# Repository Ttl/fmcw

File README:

Frequency modulated radar hardware, firmware and processing files.

For more information see:

http://hforsten.com/6-ghz-frequency-modulated-radar.html

and

http://hforsten.com/homemade-synthetic-aperture-radar.html

List of contents:

hardware: Contains KiCad schematic and board files. Made using KiCad version 2014-10-17 and might not open with a too old version.

firmware: Firmware for the Freescale Kinetis KL26Z microcontroller. Should be opened using Kinetis Design Studio (http://www.freescale.com/webapp/sps/site/prod_summary.jsp?code=KDS_IDE).

Firmware depends on mcuoneclipse components available at here: http://sourceforge.net/projects/mcuoneclipse/files/PEx%20Components/

processing: PC code for using the radar and processing the resulting data.
"fmcw.py" uses the radar and logs the data.
"fmcw_process.py" process the recorded data and plots time-range plot of them.
"list_plot.py" plots individual sweep captures from the recorded data for debugging purposes.

simulations: CST Microwave studio files.

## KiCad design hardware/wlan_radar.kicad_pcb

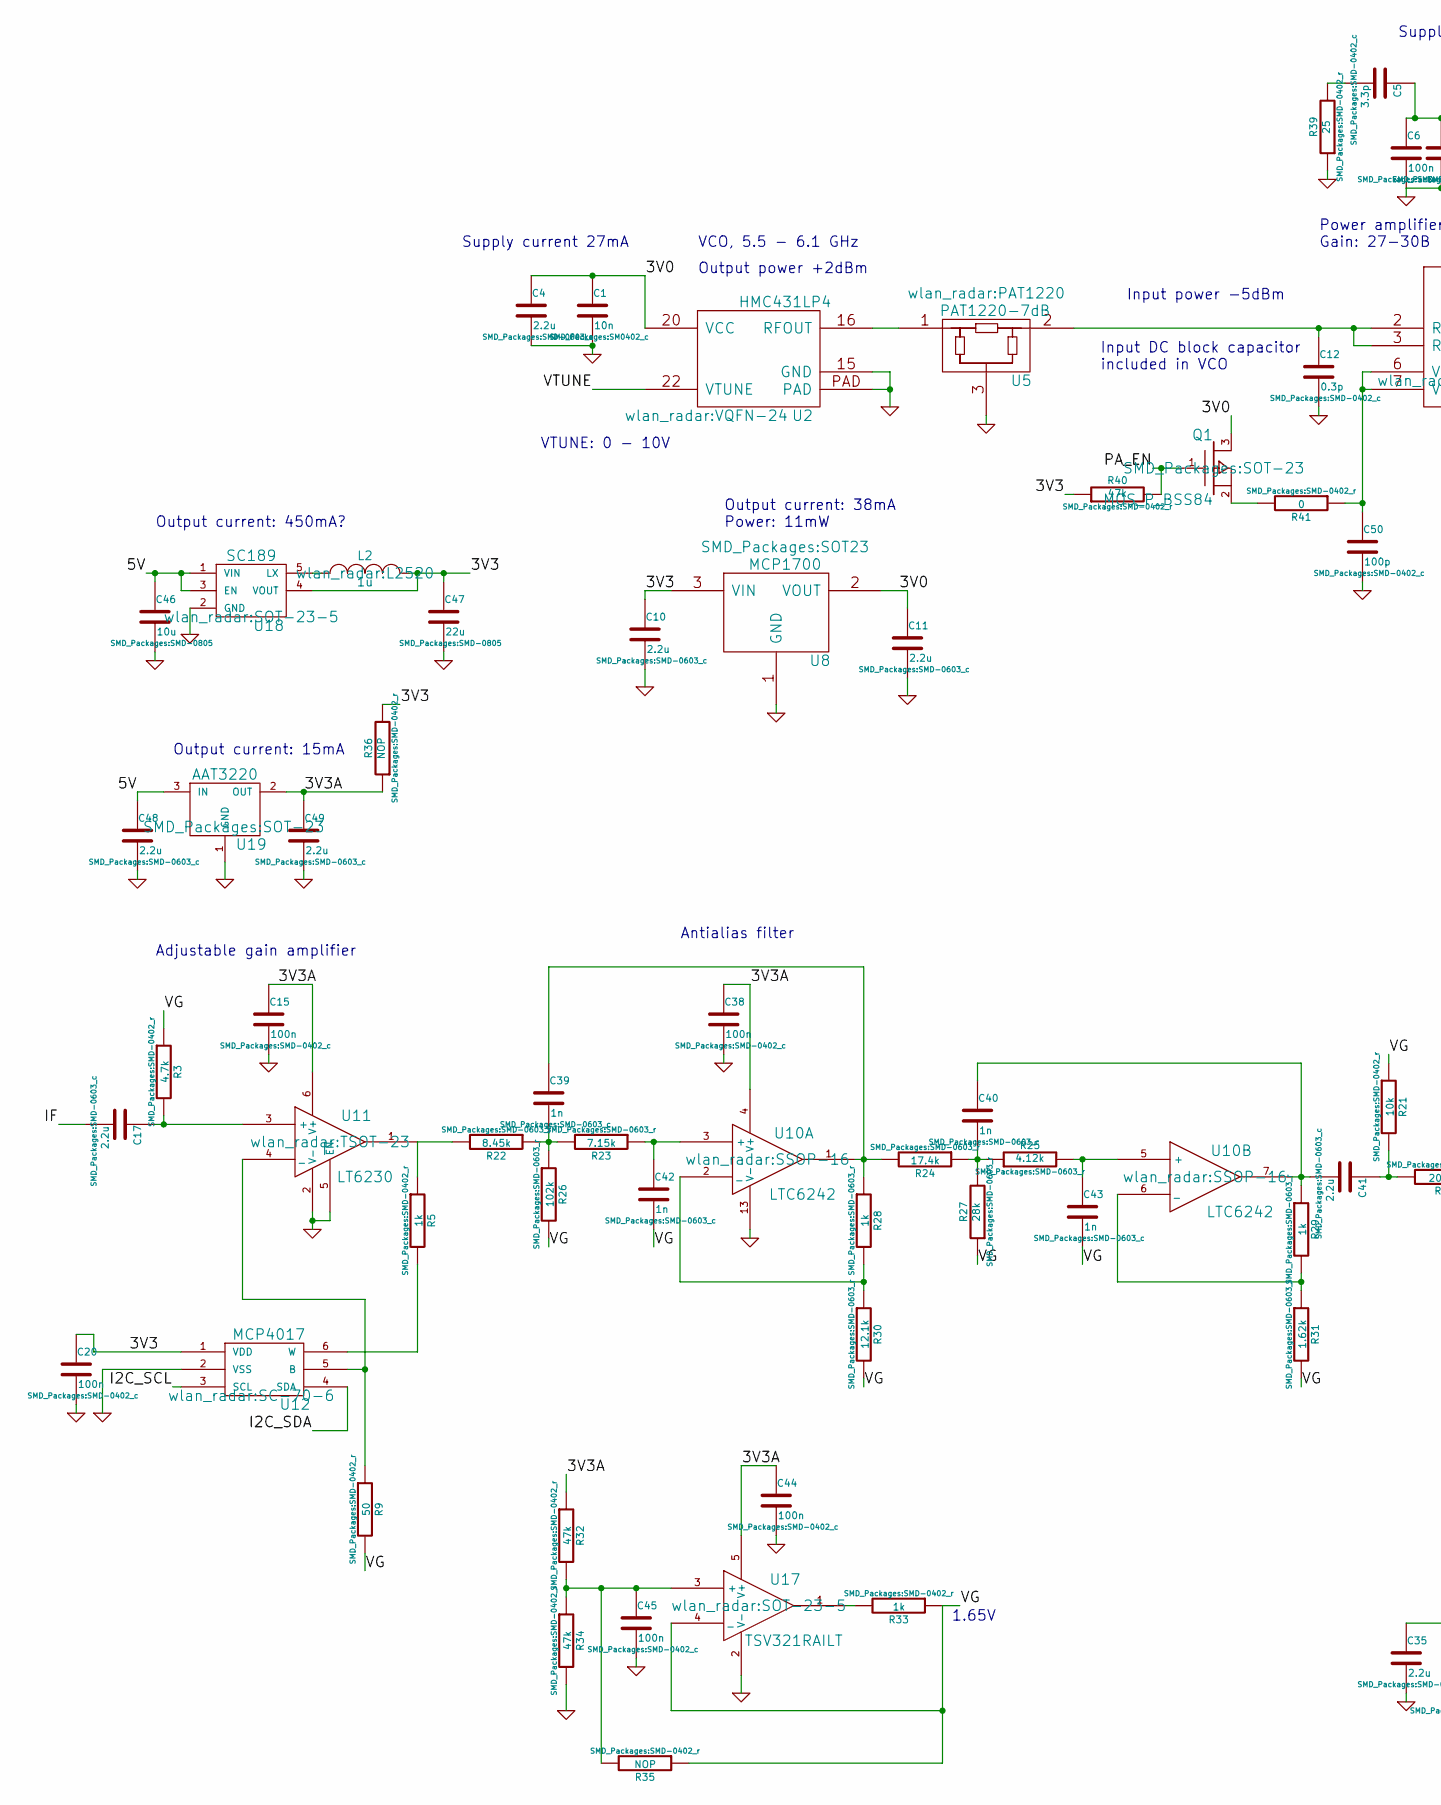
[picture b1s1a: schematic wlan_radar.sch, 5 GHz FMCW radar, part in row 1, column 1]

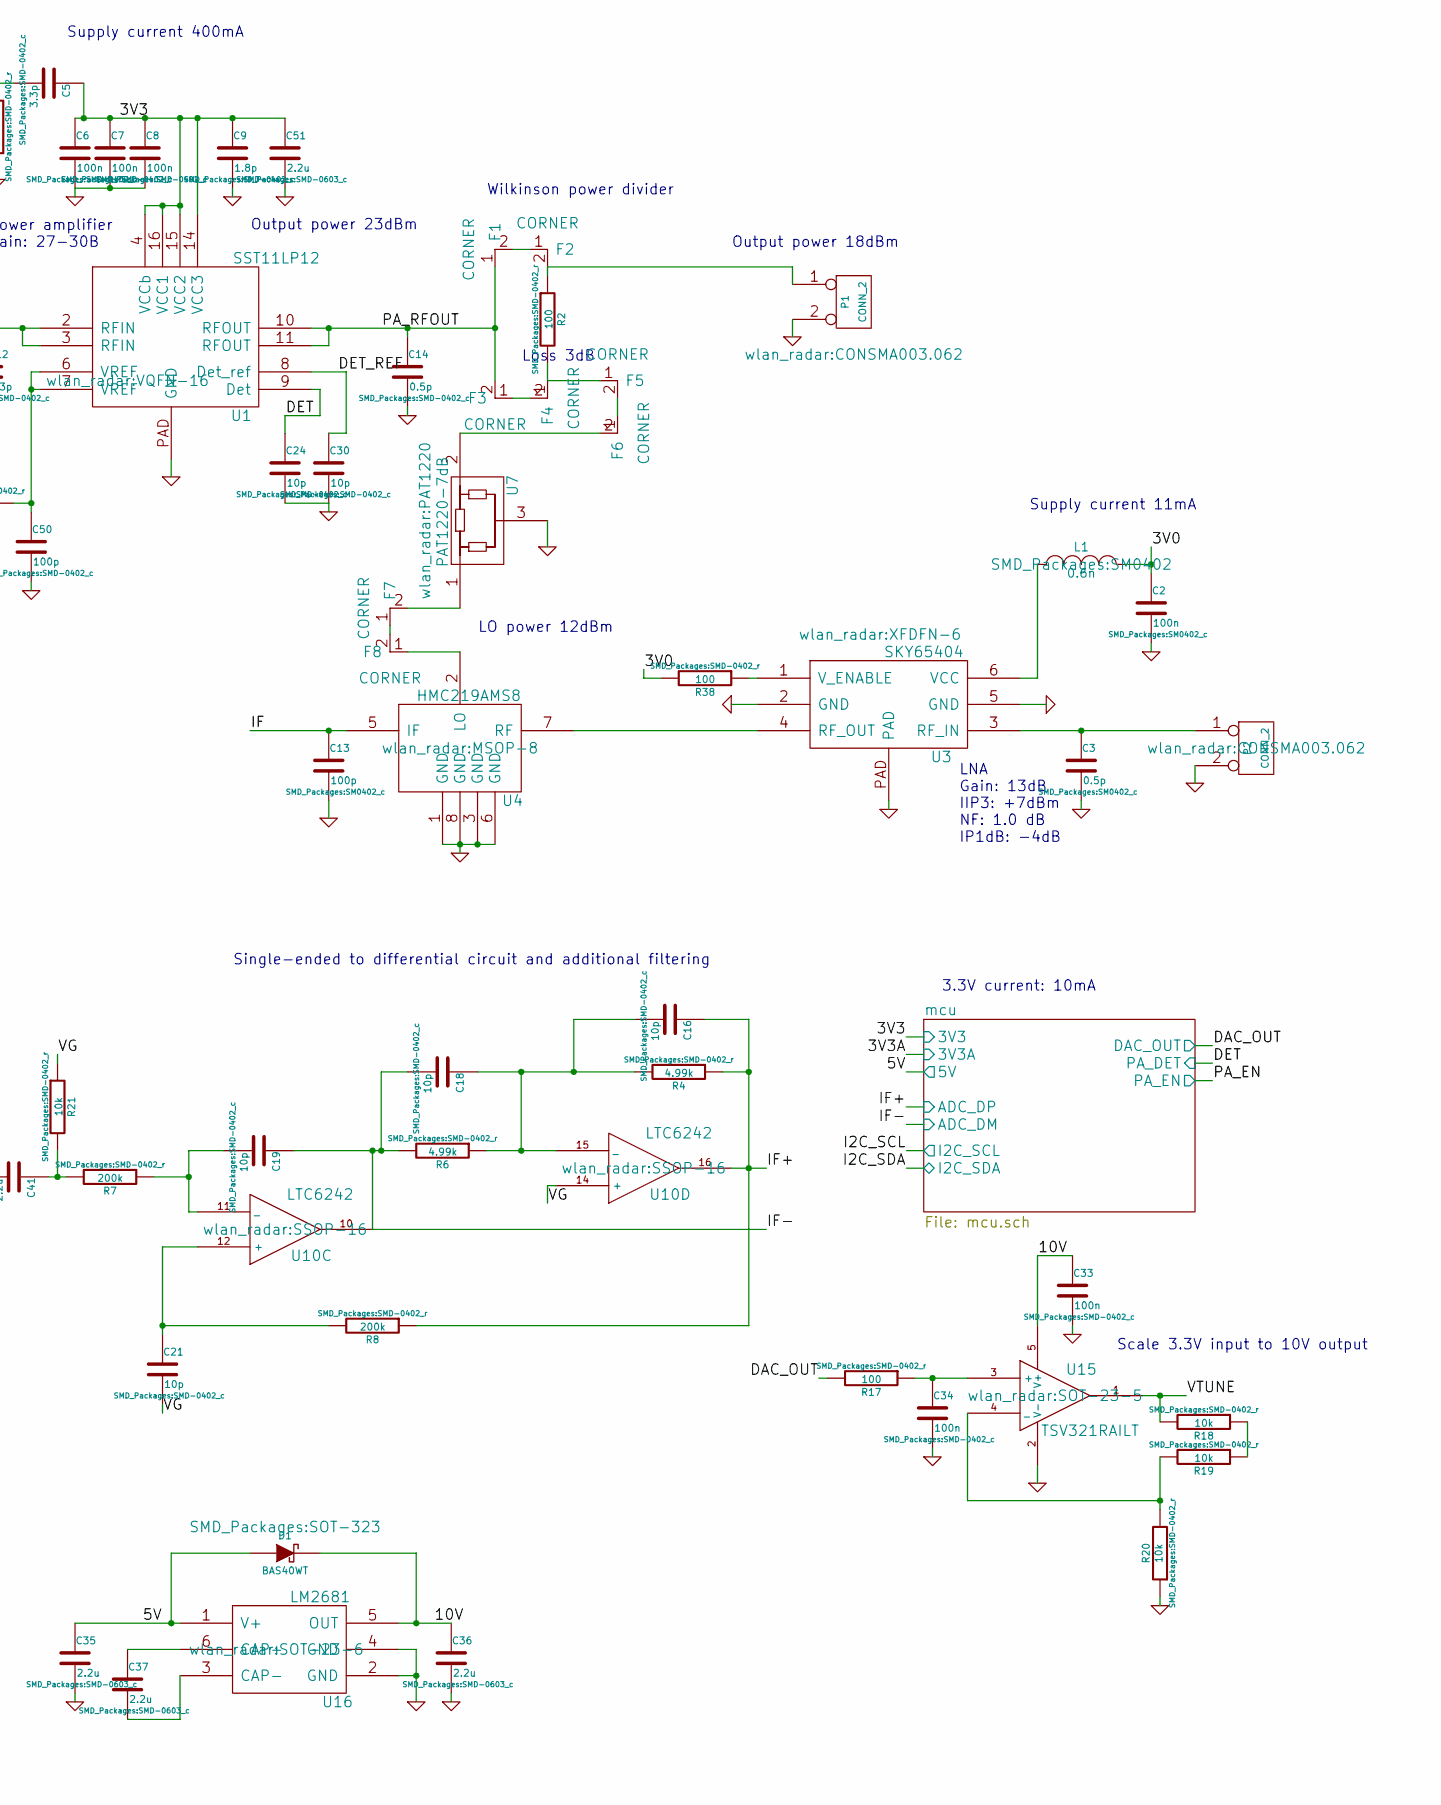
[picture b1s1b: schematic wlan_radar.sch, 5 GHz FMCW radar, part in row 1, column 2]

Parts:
C1: 10n; SM0402_c
C2: 100n; SM0402_c
C3: 0.5p; SM0402_c
C4, C10, C11, C17, C35, C36, C37, C41, C48, C49, C51: 2.2u; SMD-0603_c
C5: 3.3p; SMD-0402_c
C6, C7, C8, C15, C20, C33, C34, C38, C44, C45: 100n; SMD-0402_c
C9: 1.8p; SMD-0402_c
C12: 0.3p; SMD-0402_c
C13: 100p; SM0402_c
C14: 0.5p; SMD-0402_c
C16, C18, C19, C21, C24, C30: 10p; SMD-0402_c
C39, C40, C42, C43: 1n; SMD-0603_c
C46: 10u; SMD-0805
C47: 22u; SMD-0805
C50: 100p; SMD-0402_c
D1: BAS40WT; SOT-323
F1, F2, F3, F4: CORNER; miter_0.179_90deg
F5, F6, F7, F8: CORNER; MITER_0.350mm_90deg
L1: 0.6n; SM0402
L2: 1u; L2520
P1, P2: CONN_2; CONSMA003.062
Q1: MOS_P_BSS84; SOT-23
R2, R17, R38: 100; SMD-0402_r
R3: 4.7k; SMD-0402_r
R4, R6: 4.99k; SMD-0402_r
R5, R33: 1k; SMD-0402_r
R7, R8: 200k; SMD-0402_r
R9: 50; SMD-0402_r
R18, R19, R20, R21: 10k; SMD-0402_r
R22: 8.45k; SMD-0603_r
R23: 7.15k; SMD-0603_r
R24: 17.4k; SMD-0603_r
R25: 4.12k; SMD-0603_r
R26: 102k; SMD-0603_r
R27: 28k; SMD-0603_r
R28, R29: 1k; SMD-0603_r
R30: 12.1k; SMD-0603_r
R31: 1.62k; SMD-0603_r
R32, R34, R40: 47k; SMD-0402_r
R35, R36: NOP; SMD-0402_r
R39: 25; SMD-0402_r
R41: 0; SMD-0402_r
U1: SST11LP12; VQFN-16
U2: HMC431LP4; VQFN-24
U3: SKY65404; XFDFN-6
U4: HMC219AMS8; MSOP-8
U5, U7: PAT1220-7dB; PAT1220
U8: MCP1700; SOT23
U10: LTC6242; SSOP-16
U11: LT6230; TSOT-23
U12: MCP4017; SC-70-6
U15, U17: TSV321RAILT; SOT-23-5
U16: LM2681; SOT-23-6
U18: SC189; SOT-23-5
U19: AAT3220; SOT-23

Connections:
/3V0: C1.1, C2.1, C4.1, C11.1, L1.2, Q1.3 (D), R38.2, U2.20 (VCC), U8.2 (VOUT)
/10V: C33.1, C36.1, D1.3 (K), U15.5 (V+), U16.5 (OUT)
/DET_REF: C30.1, U1.8 (Det_ref)
/IF: C13.1, C17.2, U4.5 (IF)
/PA_RFOUT: C14.1, F1.1, F3.2, U1.10 (RFOUT), U1.11 (RFOUT)
/VG: C21.2, C42.2, C43.2, R3.1, R9.2, R21.1, R26.2, R27.1, R30.2, R31.2, R33.1, R35.1, U10.14 (+), U17.4 (_)
/VTUNE: R18.2, U2.22 (VTUNE), U15.1
/mcu/3V3: C5.1, C6.1, C7.1, C8.1, C9.1, C10.1, C20.1, C47.1, C51.1, L2.2, R36.2, R40.1, U1.4 (VCCb), U1.14 (VCC3), U1.15 (VCC2), U1.16 (VCC1), U8.3 (VIN), U12.1 (VDD), U18.4 (VOUT); also elsewhere on the board
/mcu/3V3A: C15.1, C38.1, C44.1, C49.1, R32.1, R36.1, U10.4 (V+), U11.6 (V+), U17.5 (V+), U19.2 (OUT); also elsewhere on the board
/mcu/5V: C35.1, C46.1, C48.1, D1.1 (A), U16.1 (V+), U18.1 (VIN), U18.3 (EN), U19.3 (IN); also elsewhere on the board
/mcu/ADC_DM: C18.2, C19.1, R6.2, U10.10; also elsewhere on the board
/mcu/ADC_DP: C16.1, R4.1, R8.1, U10.16; also elsewhere on the board
/mcu/DAC_OUT: R17.2; also elsewhere on the board
/mcu/I2C_SCL: U12.3 (SCL); also elsewhere on the board
/mcu/I2C_SDA: U12.4 (SDA); also elsewhere on the board
/mcu/PA_DET: C24.1, U1.9 (Det); also elsewhere on the board
/mcu/PA_EN: Q1.1 (G), R40.2; also elsewhere on the board
GND: C1.2, C2.2, C3.2, C4.2, C6.2, C7.2, C8.2, C9.2, C10.2, C11.2, C12.2, C13.2, C14.2, C15.2, C20.2, C24.2, C30.2, C33.2, C34.2, C35.2, C36.2, C38.2, C44.2, C45.2, C46.2, C47.2, C48.2, C49.2, C50.2, C51.2, P1.2 (PM), P2.2 (PM), R20.1, R34.2, R39.1, U1.PAD (GND), U2.15 (GND), U2.PAD, U3.2 (GND), U3.5 (GND), U3.PAD, U4.1 (GND), U4.3 (GND), U4.6 (GND), U4.8 (GND), U5.3, U7.3, U8.1 (GND), U10.13 (V-), U11.2 (V-), U11.5 (~EN), U12.2 (VSS), U15.2 (V-), U16.2 (GND), U16.4 (GND), U17.2 (V-), U18.2 (GND), U19.1 (GND); also elsewhere on the board
unnamed: C3.1, P2.1, U3.3 (RF_IN)
unnamed: C5.2, R39.2
unnamed: C12.1, U1.2 (RFIN), U1.3 (RFIN), U5.2
unnamed: C16.2, C18.1, R4.2, R6.1, U10.15 (_)
unnamed: C17.1, R3.2, U11.3 (+)
unnamed: C19.2, R7.1, U10.11 (_)
unnamed: C21.1, R8.2, U10.12 (+)
unnamed: C34.1, R17.1, U15.3 (+)
unnamed: C37.1, U16.6 (CAP+)
unnamed: C37.2, U16.3 (CAP-)
unnamed: C39.1, R24.2, R28.1, U10.1
unnamed: C39.2, R22.1, R23.2, R26.1
unnamed: C40.1, C41.2, R29.1, U10.7
unnamed: C40.2, R24.1, R25.1, R27.2
unnamed: C41.1, R7.2, R21.2
unnamed: C42.1, R23.1, U10.3 (+)
unnamed: C43.1, R25.2, U10.5 (+)
unnamed: C45.1, R32.2, R34.1, R35.2, U17.3 (+)
unnamed: C50.1, R41.1, U1.6 (VREF), U1.7 (VREF)
unnamed: F1.2, F2.1
unnamed: F2.2, P1.1, R2.1
unnamed: F3.1, F4.2
unnamed: F4.1, F5.1, R2.2
unnamed: F5.2, F6.1
unnamed: F6.2, U7.2
unnamed: F7.1, F8.2
unnamed: F7.2, U7.1
unnamed: F8.1, U4.2 (LO)
unnamed: L1.1, U3.6 (VCC)
unnamed: L2.1, U18.5 (LX)
unnamed: Q1.2 (S), R41.2
unnamed: R5.2, U12.6 (W)
unnamed: R9.1, U11.4 (_), U12.5 (B)
unnamed: R18.1, R19.1
unnamed: R19.2, R20.2, U15.4 (_)
unnamed: R5.1, R22.2, U11.1
unnamed: R28.2, R30.1, U10.2 (_)
unnamed: R29.2, R31.1, U10.6 (_)
unnamed: R33.2, U17.1
unnamed: R38.1, U3.1 (V_ENABLE)
unnamed: U2.16 (RFOUT), U5.1
unnamed: U3.4 (RF_OUT), U4.7 (RF)

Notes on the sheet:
VCO, 5.5 - 6.1 GHz
Output power +2dBm
Wilkinson power divider
Power amplifier Gain: 27-30B
Input power -5dBm
Output power 23dBm
Loss 3dB
Output power 18dBm
LO power 12dBm
LNA Gain: 13dB IIP3: +7dBm NF: 1.0 dB IP1dB: -4dB
Supply current 400mA
Supply current 27mA
VTUNE: 0 - 10V
Supply current 11mA
Output current: 38mA Power: 11mW
Scale 3.3V input to 10V output
1.65V
Adjustable gain amplifier
Antialias filter
Single-ended to differential circuit and additional filtering
Output current: 15mA
Output current: 450mA?
Input DC block capacitor included in VCO
3.3V current: 10mA

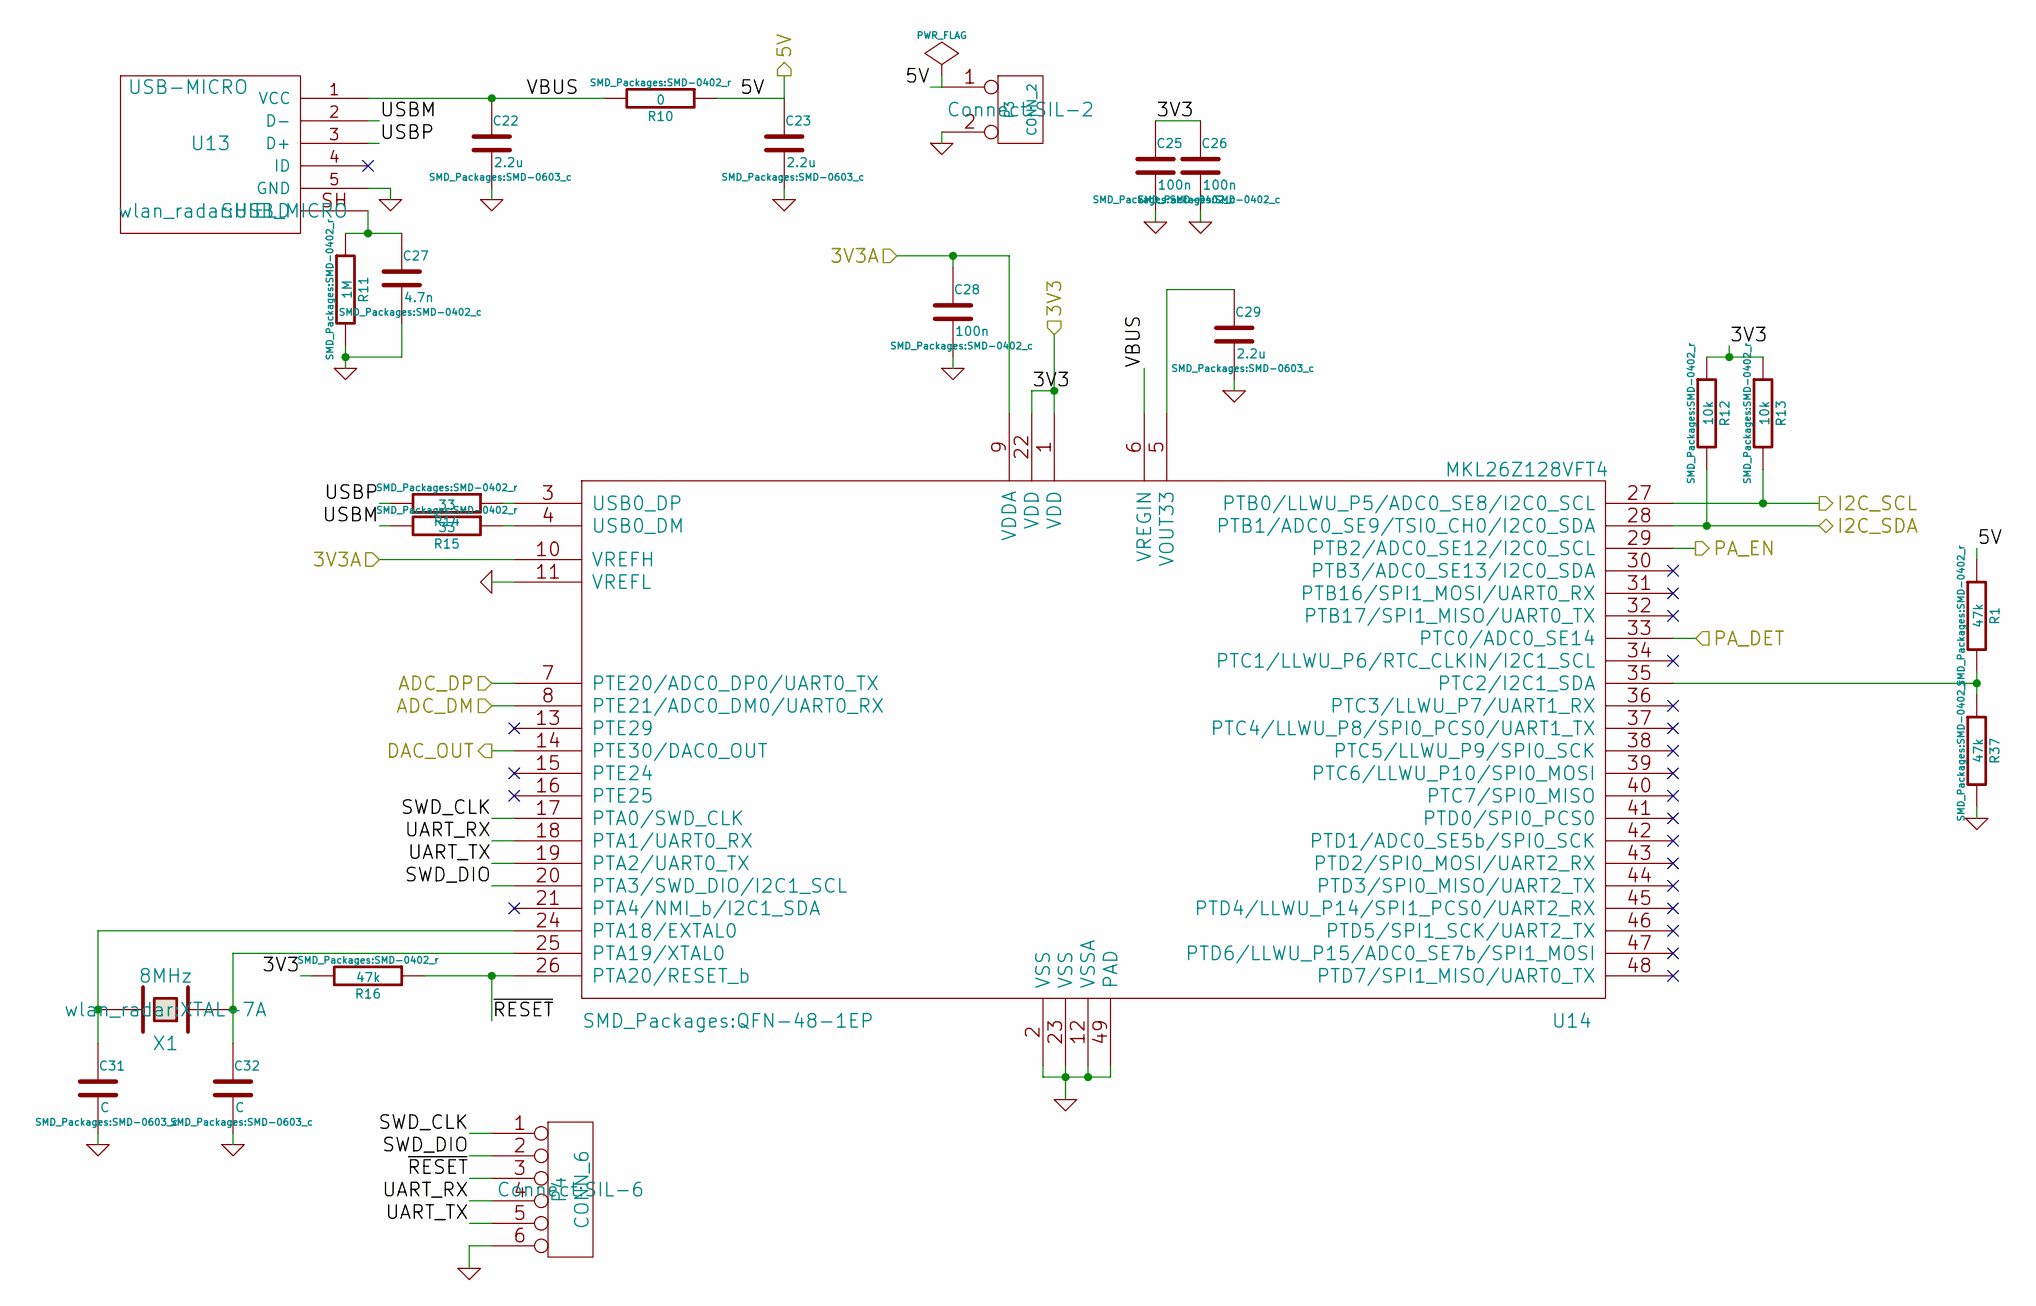
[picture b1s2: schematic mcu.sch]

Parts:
C22, C23, C29: 2.2u; SMD-0603_c
C25, C26, C28: 100n; SMD-0402_c
C27: 4.7n; SMD-0402_c
C31, C32: C; SMD-0603_c
P3: CONN_2; SIL-2
P4: CONN_6; SIL-6
R1, R16, R37: 47k; SMD-0402_r
R10: 0; SMD-0402_r
R11: 1M; SMD-0402_r
R12, R13: 10k; SMD-0402_r
R14, R15: 33; SMD-0402_r
U13: USB-MICRO; USB_MICRO
U14: MKL26Z128VFT4; QFN-48-1EP
X1: 8MHz; XTAL-7A

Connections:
/mcu/3V3: C25.1, C26.1, R12.1, R13.1, R16.2, U14.1 (VDD), U14.22 (VDD); also elsewhere on the board
/mcu/3V3A: C28.1, U14.9 (VDDA), U14.10 (VREFH); also elsewhere on the board
/mcu/5V: C23.1, P3.1, R1.1, R10.1; also elsewhere on the board
/mcu/ADC_DM: U14.8 (PTE21/ADC0_DM0/UART0_RX); also elsewhere on the board
/mcu/ADC_DP: U14.7 (PTE20/ADC0_DP0/UART0_TX); also elsewhere on the board
/mcu/DAC_OUT: U14.14 (PTE30/DAC0_OUT); also elsewhere on the board
/mcu/I2C_SCL: R13.2, U14.27 (PTB0/LLWU_P5/ADC0_SE8/I2C0_SCL); also elsewhere on the board
/mcu/I2C_SDA: R12.2, U14.28 (PTB1/ADC0_SE9/TSI0_CH0/I2C0_SDA); also elsewhere on the board
/mcu/PA_DET: U14.33 (PTC0/ADC0_SE14); also elsewhere on the board
/mcu/PA_EN: U14.29 (PTB2/ADC0_SE12/I2C0_SCL); also elsewhere on the board
/mcu/SWD_CLK: P4.1, U14.17 (PTA0/SWD_CLK)
/mcu/SWD_DIO: P4.2, U14.20 (PTA3/SWD_DIO/I2C1_SCL)
/mcu/UART_RX: P4.4, U14.18 (PTA1/UART0_RX)
/mcu/UART_TX: P4.5, U14.19 (PTA2/UART0_TX)
/mcu/USBM: R15.2, U13.2 (D-)
/mcu/USBP: R14.2, U13.3 (D+)
/mcu/VBUS: C22.1, R10.2, U13.1 (VCC), U14.6 (VREGIN)
/mcu/~RESET: P4.3, R16.1, U14.26 (PTA20/RESET_b)
GND: C22.2, C23.2, C25.2, C26.2, C27.2, C28.2, C29.2, C31.2, C32.2, P3.2 (PM), P4.6, R11.2, R37.2, U13.5 (GND), U14.2 (VSS), U14.11 (VREFL), U14.12 (VSSA), U14.23 (VSS), U14.49 (PAD); also elsewhere on the board
unnamed: C27.1, R11.1, U13.SH (SHIELD)
unnamed: C29.1, U14.5 (VOUT33)
unnamed: C31.1, U14.24 (PTA18/EXTAL0), X1.2
unnamed: C32.1, U14.25 (PTA19/XTAL0), X1.1
unnamed: R1.2, R37.1, U14.35 (PTC2/I2C1_SDA)
unnamed: R14.1, U14.3 (USB0_DP)
unnamed: R15.1, U14.4 (USB0_DM)

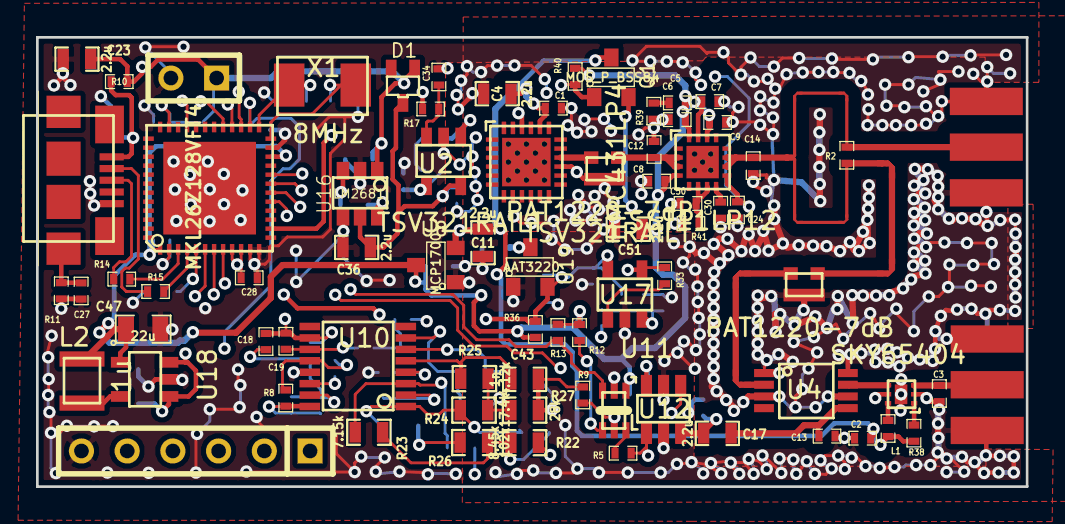
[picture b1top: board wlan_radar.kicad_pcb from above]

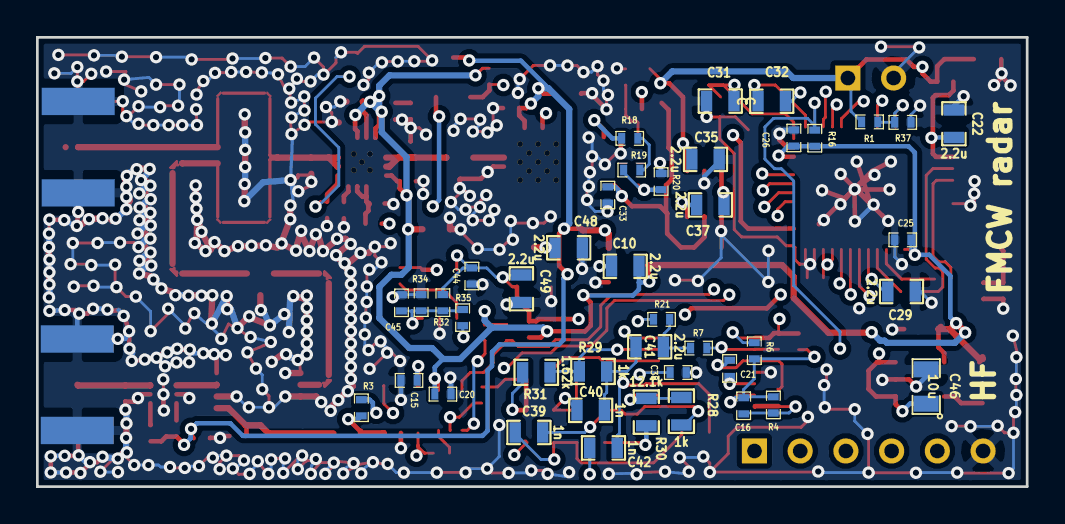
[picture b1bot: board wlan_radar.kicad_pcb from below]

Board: 4 copper layers, 55.0 x 25.0 mm, 126 parts (42 on the bottom side), 75 nets.

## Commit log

2014-12-02 Add link to the blog post
2014-12-04 Fix hardware mistakes
    This commit adds fixes some of the mistakes identified after the
    board was ordered.
    Add 100n capacitor to MCUs reset pin to fix programming issues.
    Add series connection of resistor and capacitor in parallel
    with mixer output amplifier to fix the DC balance issue.
    Remove the now unneeded capacitor and resistor
2014-12-13 Add CST simulation files
2014-12-30 Add bill of materials
2014-12-30 Use non-zero update interval
    0 interval doesn't work on my laptop though desktop computer
    is fine with it.
2015-08-08 Increase USB buffer size
    TX and RX buffers were previously only 1 bytes each.
    Increasing buffer sizes increases communication relability and speed.
2015-08-10 Don't throw away samples
    Due to discontinuity in the sweep there can be a big spike
    in the amplitude at the beginning of the sweep. Now first
    third of the samples are not taken into consideration in autogain
    algorithm.
    Reduce ADC sampling rate, because previous one was too high considering
    the maximum range of the radar.
2015-11-25 Add library cache
    Solves issue #3
2015-12-09 Assign values to crystal load capacitors (33p)
    Add 100n capacitors to BOM
2016-01-15 Add note about firmware dependencies
2016-10-30 Fix distance calculation
